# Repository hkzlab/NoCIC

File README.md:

# NoCIC

## DISCLAIMER

Any use of this project is **under your own responsibility**.
You will be responsible of checking the correct construction and functionality of your board.
By using this project You will agree that I cannot be held responsible if it will destroy any of your devices, damage your computer, burn down your house or whatever.

### Sponsorship

This project is kindly sponsored by [PCBWay](https://pcbway.com).
PCBWay specializes in manufacturing high-quality PCBs and makes them affordable to hobbyist and professionals alike.

The range of services they offer include PCB prototyping, assembly, instant quotes for your order, a verification process by a team
of experts and an easy to use, hassle-free order process.

I'm grateful to PCBWay for the help in evolving and testing this project. You can order the currently released revisions of the board from them, see the link below!

## Introduction

This is a replacement of the NES CIC IC that implements the reset functionality, fits in a DIP16 footprint and... nothing else.

The [NullCIC](https://github.com/Redherring32/NullCIC/) already does this, but I faced some issues with it where the NES sometimes failed to startup properly during
a cold boot, and required a manual reset (possibly related to timing of my specific motherboard, even though the issues were not present with an original CIC installed).

Tweaking the cap and bodging a resistor on the NullCIC alleviated the issue by a lot, but I decided to go with something that allowed me to control the reset timing
a bit more reliably, and went with a classic 555 circuit.

The values for the components in the BOM should provide around 500ms of time in reset at startup.

This board was tested with two of my NES units without issues, let me know if it works for you!

## Hardware

The board was designed with [KiCad](https://kicad.org/) EDA.

### Bill of Materials

| Component              | Qty | Type / Value                                            | Notes                                                                |
| ---------------------- | --- | ------------------------------------------------------- | -------------------------------------------------------------------- |
| U1                     |  1  | 74LVC1G06 / SOT-23-5                                    |                                                                      |
| U2                     |  1  | 555, CMOS, SOIC-8                                       |                                                                      |
| U3                     |  1  | 74LVC1G04 / SOT-23-5                                    |                                                                      |
| C1, C4                 |  2  | 100nF / 16V+ / 0805                                     | MLCC                                                                 |
| C2                     |  1  | 10nF / 16V+ / 0805                                      | MLCC                                                                 |
| C3                     |  1  | 10uF / 16V+ / 0805                                      | MLCC                                                                 |
| C5                     |  1  | 470nF / 16V+ / 0805                                     | MLCC                                                                 |
| R1                     |  1  | 10K / 0805                                              |                                                                      |
| R2                     |  1  | 1M / 0805                                               |                                                                      |
| R3                     |  1  | 47K / 0805                                              |                                                                      |
| R4, R5                 |  2  | 2K ~ 10K / 0805                                         | Optional pull-downs for DI and DO, in case a fake CIC in the cart attempts to glitch us with spikes                  |
| J1                     |  2  | 8pin machined headers, 2.54mm pitch                     | Mount on the underside                                               |

JP1 can be optionally jumpered to allow the 555 to reset the CIC in the cart.

### Ordering the boards

You can order the board for this project at [PCBWay](https://www.pcbway.com/project/shareproject/NoCIC_Replacement_NES_CIC_8e238847.html) and support me or download 
the gerbers and have them printed wherever you like!!!

## TODO

- There are some "[reports](https://consolemods.org/wiki/NES:Disabling_CIC_Chip)" of overheating for games that attempt to glitch the CIC with voltage spikes if the CIC is not there. Find a way to test this with those games?

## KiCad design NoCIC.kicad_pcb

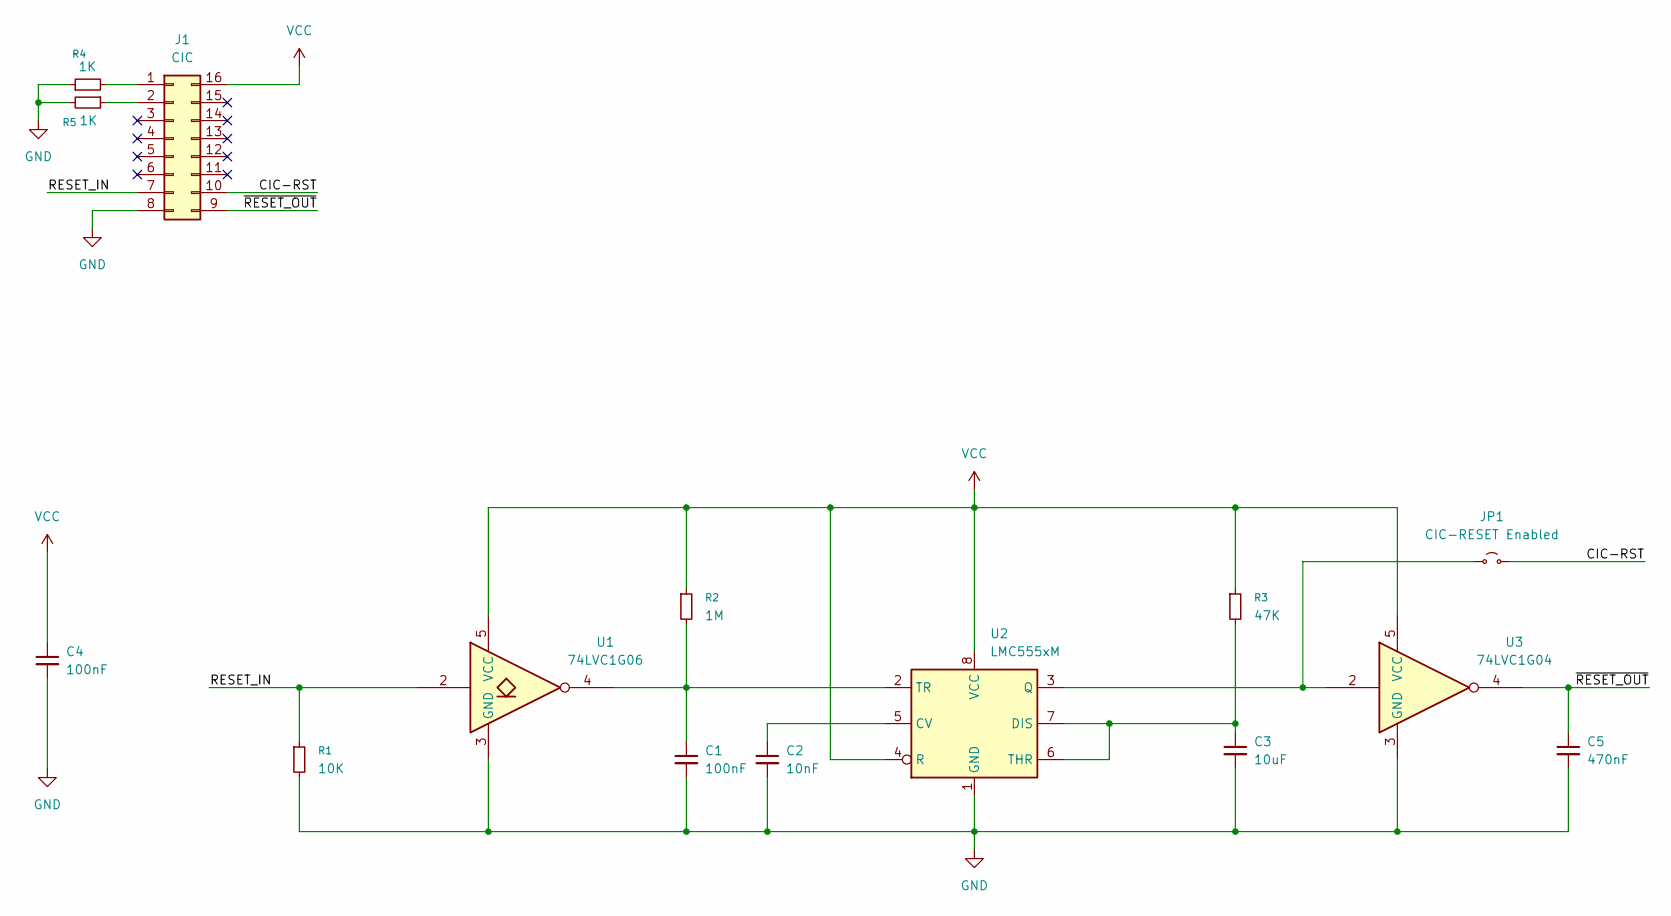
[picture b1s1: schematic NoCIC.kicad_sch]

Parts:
C1, C4: 100nF; C_0805_2012Metric_Pad1.18x1.45mm_HandSolder
C2: 10nF; C_0805_2012Metric_Pad1.18x1.45mm_HandSolder
C3: 10uF; C_0805_2012Metric_Pad1.18x1.45mm_HandSolder
C5: 470nF; C_0805_2012Metric_Pad1.18x1.45mm_HandSolder
J1: CIC; DIP-16_W7.62mm
JP1: CIC-RESET Enabled; SolderJumper-2_P1.3mm_Open_RoundedPad1.0x1.5mm
R1: 10K; R_0805_2012Metric_Pad1.20x1.40mm_HandSolder
R2: 1M; R_0805_2012Metric_Pad1.20x1.40mm_HandSolder
R3: 47K; R_0805_2012Metric_Pad1.20x1.40mm_HandSolder
R4, R5: 1K; R_0805_2012Metric_Pad1.20x1.40mm_HandSolder
U1: 74LVC1G06; SOT-23-5
U2: LMC555xM; SOIC-8_3.9x4.9mm_P1.27mm
U3: 74LVC1G04; SOT-23-5

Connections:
/CIC-RST: J1.10, JP1.2 (B)
/RESET_IN: J1.7, R1.1, U1.2
/~RESET_OUT: C5.1, J1.9, U3.4
GND: C1.2, C2.2, C3.2, C4.2, C5.2, J1.8, R1.2, R4.1, R5.2, U1.3 (GND), U2.1 (GND), U3.3 (GND)
unnamed: J1.1, R4.2
unnamed: J1.2, R5.1
unnamed: JP1.1 (A), U2.3 (Q), U3.2
unnamed: C2.1, U2.5 (CV)
unnamed: C3.1, R3.2, U2.6 (THR), U2.7 (DIS)
unnamed: C1.1, R2.2, U1.4, U2.2 (TR)
VCC: C4.1, J1.16, R2.1, R3.1, U1.5 (VCC), U2.4 (R), U2.8 (VCC), U3.5 (VCC)

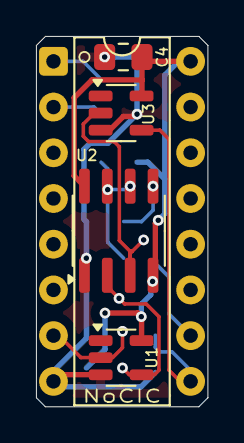
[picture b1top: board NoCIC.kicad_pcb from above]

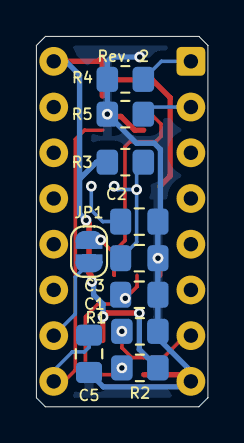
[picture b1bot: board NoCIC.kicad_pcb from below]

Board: 2 copper layers, 9.5 x 20.6 mm, 15 parts (10 on the bottom side), 11 nets.

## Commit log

2025-05-29 Add base NoCIC
2025-06-27 Add basic README
2025-06-27 move pics
2025-06-27 Resize pic
2025-06-27 Update the README
2025-06-27 Fix typo
2025-06-27 Fix duplicated U3 in readme
2025-06-27 Add a jumper option to connect 555 output to pin 10, for CIC-RESET
2025-06-27 Add load resistors on data lines
2025-06-27 Add comments to README
2025-07-29 generate gerber for rev.2
2025-07-31 Mention PCBWay sponsorship!
